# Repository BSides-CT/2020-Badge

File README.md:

# 2020-Badge
Source code, schematics, and advice for hacking the 2020 BSidesCT electronic badge.

## TL;DR

- Software to blink the LEDs on the badge is functional, and you can get it here: [Software/LEDBlink](https://github.com/BSides-CT/2020-Badge/tree/main/Software/LEDBlink)
- Software to use the NFC reader on the badge is not functional, and you can get it here: [Software/NFCBadge](https://github.com/BSides-CT/2020-Badge/tree/main/Software/NFCBadge)
- Read on for more information about what works, what doesn't, and what challenges you are likely to encounter while hacking the badge.

## The Long and Sad Tale of the BSidesCT ~~2019~~ 2020 Badge

### Part 1: Prologue

It started in 2019 when we had a great idea to make a badge with an NFC card reader built into it. We were inspired by the [NFCopy85](https://salmg.net/2019/06/16/nfcopy85/) project and wanted to do something like it. After all, how cool would it be to use your BSidesCT badge to replay hotel key cards, smart locks, or credit card transactions?!

We designed the badge, ordered the PCBs, and started working on the software. We thought we gave sufficient lead time for the boards to be cut and shipped from China...but alas, they arrived to late to be distributed at last year's conference (hence the swell DIY badges we ~~threw together at the last possible second~~ ended up with).

As it turns out, we were doomed to failure last year – even if the badges had arrived on time, we could not have anticipated the other problems we had yet to discover....

### Part 2: Down the Rabbit Hole

The PCBs and other parts finally arrived after BSidesCT 2019 had come and gone, but we found solace in the idea that we could finish them for distribution in 2020. Unfortunately for us, a couple of things made that effort significantly harder:

1. The badge's original designer ghosted us, leaving the 2020 team without design schematics.
2. No working software had yet been produced.

Undeterred, we set out to crack this nut, or at the very least make some LEDs blink. It was pretty obvious from examining the board and components that it had been designed with three main features:

- Cortex-based microcontroller
- NFC chip
- USB-C port

There were also six contact pads arranged in a way that looked like Serial Wire Debug (SWD/JTAG), which should provide a way to program the microcontroller.

From there, we started examining traces, mapping pins, testing connectivity, and generally trying to figure out What Stuff Does™. After many interations and improvements, we finally identified the exact components and pinouts in use. Without further ado, here they are.

#### Microcontroller: Atmel SAM D11 D14AM

- [Datasheet summary](https://github.com/BSides-CT/2020-Badge/blob/main/Hardware/Atmel-SAM-D11-Summary.pdf)
- [Datasheet](https://github.com/BSides-CT/2020-Badge/blob/main/Hardware/Atmel-SAM-D11-Datasheet.pdf)
- Pinout:

#### NFC: CR95HF

- [Datasheet](https://github.com/BSides-CT/2020-Badge/blob/main/Hardware/CR95HF-Datasheet.pdf)
- Pinout:

We did not identify any additional storage components, so the 16 KB of flash storage available on the SAMD11 was all we would have to work with.

In order to program the badge, we acquired a [J-Link EDU Mini](https://www.segger.com/products/debug-probes/j-link/models/j-link-edu-mini/) (later replaced with an [Atmel ICE](https://www.microchip.com/DevelopmentTools/ProductDetails/atatmel-ice)) and relied on our trusty multimeter to map the SWD pinout on the PCB:

We soldered on some wires, plugged them into the J-Link, and fired up [Atmel Studio](https://www.microchip.com/mplab/avr-support/atmel-studio-7) to write some code.

### Part 3: Progress at Last!

Thanks to Atmel Start, it was pretty simple at that point to load up some basic drivers for the SAMD11AM, identify which pins had LEDs attached to them, and write some basic code to make them blink. The J-Link worked like a charm for this simple task.

We added in some functions to make the LEDs blink in fun patterns and decided that, if nothing else, at least we could ship the badges with [that simple program](https://github.com/BSides-CT/2020-Badge/tree/main/Software/LEDBlink). Feel free to customize it to blink however you want it to!

### Part 4: Straight into a Wall

Having enjoyed a fleeting moment of accomplishment, we got back to work on trying to figure out how to get the other components working. The initial goals were pretty simple:

1. Have the CR95HF scan until it found an NFC tag it recognized.
2. Output feedback while scanning to a serial terminal over USB.

Fortunately, Atmel Start also makes it pretty simple to support these features. From the traces on the PCB, we were able to determine that the MCU was intended to communicate with the CR95HF via SPI and not UART, so we knew we would need SPI drivers. We also learned that in order to have the USB port be recognized by another device (i.e. a computer) as a serial terminal (virtual COM port), we would need to configure it as a CDC device.

We configured Atmel Start with the appropriate drivers, mapped the pins appropriately, and then spent a lot of time fussing with the clock configurations (and datasheets) to get everything playing nicely. In the end, this is what our driver stack and clock configs looked like:

The project compiled successfully with the USB drivers, and when we plugged the badge into a computer, it showed up as a COM port in the Device Manager (hooray!). Unfortunately, this is where our luck began to run out. We tried to get the badge to print simple text messages to serial output over USB, but no matter how we attempted to connect to the virtual terminal (or at what baud rate), no messages were ever displayed. We did some troubleshooting and were able to determine that the USB drivers initiated successfully and the serial write function completed successfully, so we were mystified about where communication broke down.

### Part 5: Left Hanging

Not longer after this development, we finally managed to get in touch with the original designer, who sent us the [KiCad design schematics](https://github.com/BSides-CT/2020-Badge/tree/main/Hardware/Schematics) and non-functioning prototype software. This information confirmed many of the determinations we had made, corrected several of our mistakes, and gave us a jump on the software to use to run the CR95HF. Unfortunately, despite being able to integrate much of that code into our own project, we quickly ran into a deal-breaker as the CR95HF failed to initialize. Without serial output, of course, we found this exceedingly hard to debug, and mostly relied on the LEDs to test whether specific functions succeeded or failed.

In the end, we ran out of time and decided it would be best to deliver the badges with some nice blinking lights and a link to a GitHub repo with all the information one needs to pick up where we left off. There is a still a great deal of potential in this project for those who are more knowledgable than our scrappy band of misfits!

Our hope is that someone will solve one or two of the problems that held us up and find a way to make the badge do something more interesting than just blink its LEDs! If that person is you, please reach out to us at info@bsidesct.org and we'll be excited to trade notes.

### Epilogue: Known Issues

Along the way, we discovered several problems that stopped us from reaching our initial goal. Here they are, for the reader's edification:

- We were unable to get USB working as a functional virtual com port. The designer suspected there might have been a design or manufacturing flaw involved, but this year's team did not have enough electrical engineering knowledge to verify this. You can power the badge via USB.

- We were unable to get the CR95HF to initalize successfully. The initialization sequence involves a loop that continually tests for a response from the chip before moving on, but it never escapes that loop.

- While testing basic components, we started to run out of storage space. If you manage to get the NFC chip functional, it is likely you will need to get creative about managing data to make the badge do anything interesting.

- Programming the badges en masse proved to be a challenge, as the SWD pin pads do not map to any standard configuration. As such, we had to build our own adapter to remap the standard 10-pin cable from our Atmel ICE programmer to a standard 6-pin TC2030 programming cable.

  We don't recommend doing it this way, which was only really necessary for mass production – you're better off just soldering wires onto the badge to program it. Follow the SWD pinout we posted above, and you should be good to go!

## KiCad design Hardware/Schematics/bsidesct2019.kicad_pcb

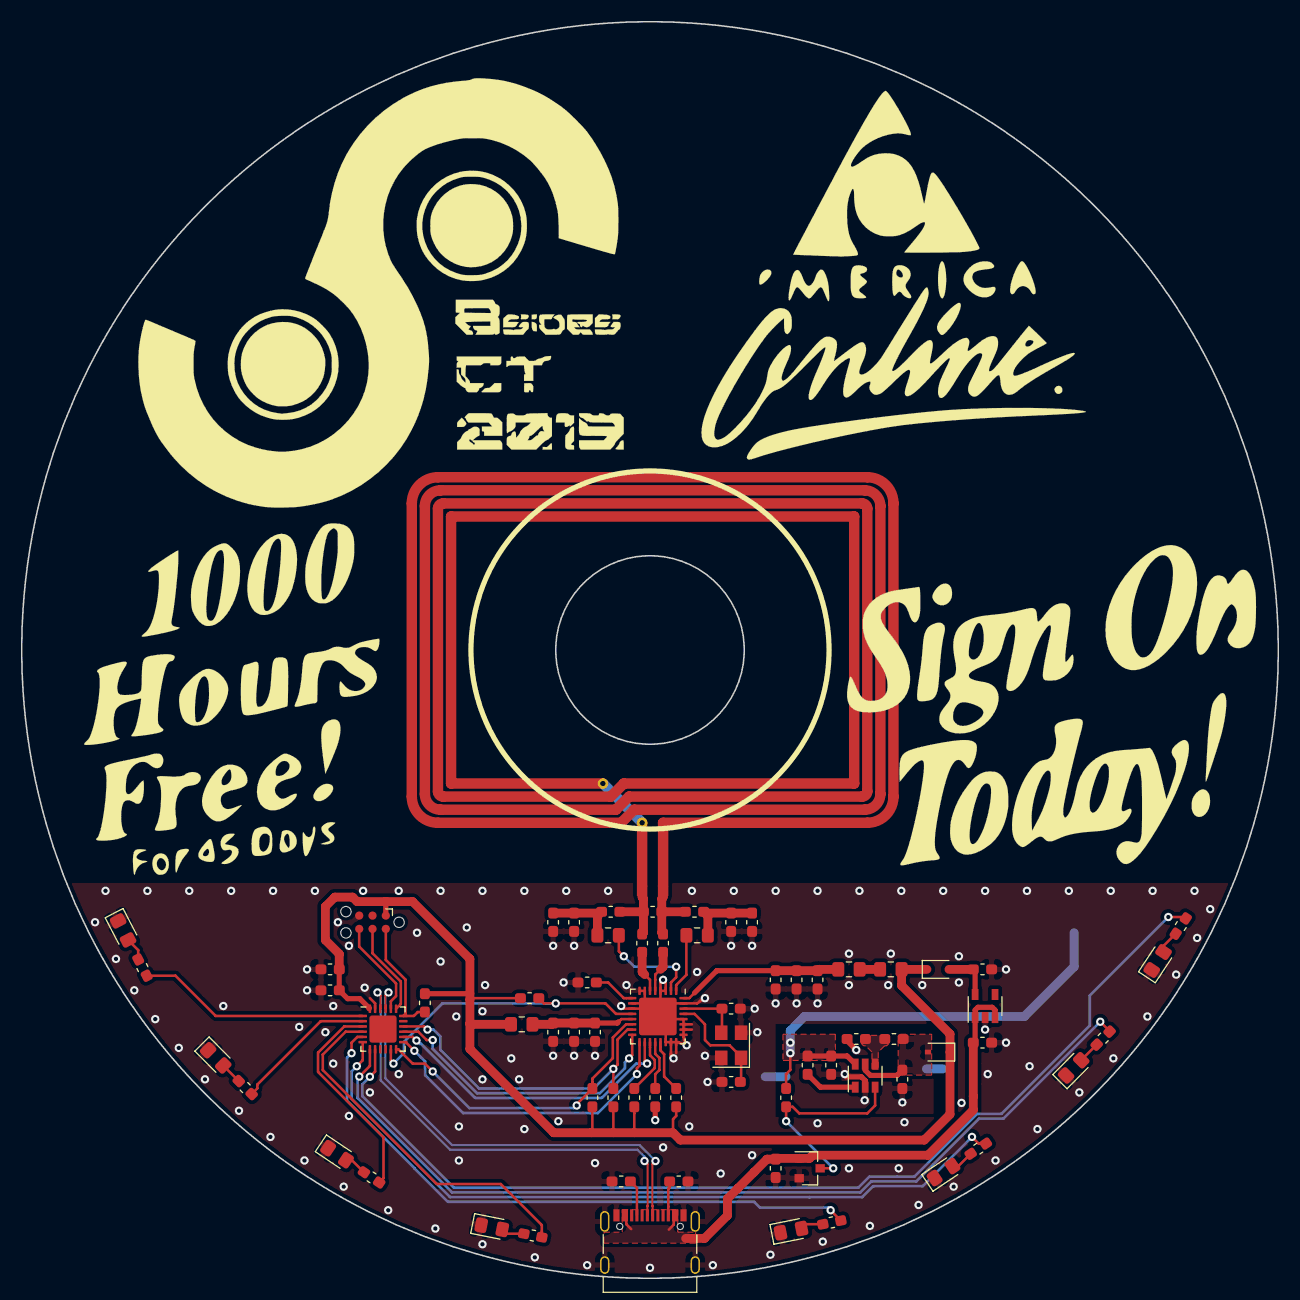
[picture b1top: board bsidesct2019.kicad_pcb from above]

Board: 2 copper layers, 120.0 x 120.0 mm, 75 parts (1 on the bottom side), 55 nets.

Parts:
AE1: Antenna; CR95HF-antenna
C1, C2, C18, C21, C22: 1uF; C_0603_1608Metric_Pad1.05x0.95mm_HandSolder
C3, C4, C10: 0.1uF; C_0603_1608Metric_Pad1.05x0.95mm_HandSolder
C5, C9: 10pF; C_0603_1608Metric_Pad1.05x0.95mm_HandSolder
C6, C7: 10nF; C_0603_1608Metric_Pad1.05x0.95mm_HandSolder
C8: 1nF; C_0603_1608Metric_Pad1.05x0.95mm_HandSolder
C11, C12, C13, C14: 100pF; C_0603_1608Metric_Pad1.05x0.95mm_HandSolder
C15, C16: 47pF; C_0603_1608Metric_Pad1.05x0.95mm_HandSolder
C17: 82pF; C_0603_1608Metric_Pad1.05x0.95mm_HandSolder
C19: 4.7uF; C_0603_1608Metric_Pad1.05x0.95mm_HandSolder
C20: 10uF; C_0603_1608Metric_Pad1.05x0.95mm_HandSolder
D1, D10: CUS10S30,H3F; D_SOD-323
D2, D3, D4, D5, D6, D7, D8, D9: LED; LED_0805_2012Metric_Pad1.15x1.40mm_HandSolder
J1: TC2030; Tag-Connect_TC2030-IDC-NL_2x03_P1.27mm_Vertical
L1, L2, L3: 742792042; L_0805_2012Metric_Pad1.15x1.40mm_HandSolder
L4, L5: 560nH; L_0805_2012Metric_Pad1.15x1.40mm_HandSolder
L6: 4.7uH; L_0603_1608Metric_Pad1.05x0.95mm_HandSolder
P1: USB_C_Plug_USB2.0; USB_C_Receptacle_Palconn_UTC16-G
Q1: 2N7002; SOT-23
R1, R2, R3, R4, R5, R15: 3.3kΩ; R_0603_1608Metric_Pad1.05x0.95mm_HandSolder
R6, R7: 330Ω; R_0603_1608Metric_Pad1.05x0.95mm_HandSolder
R8, R13, R14: 10kΩ; R_0603_1608Metric_Pad1.05x0.95mm_HandSolder
R9, R10: 5.1kΩ; R_0603_1608Metric_Pad1.05x0.95mm_HandSolder
R11: 976kΩ; R_0603_1608Metric_Pad1.05x0.95mm_HandSolder
R12: 562kΩ; R_0603_1608Metric_Pad1.05x0.95mm_HandSolder
R16, R17, R18, R19, R20, R21, R22, R23: 260Ω; R_0603_1608Metric_Pad1.05x0.95mm_HandSolder
Ref**: Val**; twitter
Ref**#2: Val**; aol_3
Ref**#3: Val**; aol_2
Ref**#4: Val**; aol_1-merica
Ref**#5: Val**; bsidesct.2019.logo.transparent
U1: CR95HF; QFN-32-1EP_5x5mm_P0.5mm_EP3.6x3.6mm
U2: MCP1640BCH; SOT-23-6
U3: ATSAMD11D14A-M; QFN-24-1EP_4x4mm_P0.5mm_EP2.6x2.6mm
U4: MIC5504-3.3YM5-TR; SOT-23-5
Y1: 27.12MHz; Crystal_SMD_SeikoEpson_FA238V-4Pin_3.2x2.5mm

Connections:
+3V3: C10.1, C18.1, D1.1, D10.1, J1.1, L1.1, L3.1, R1.1, R2.1, R3.1, R5.1, R8.1, R15.1, U3.24
+5V: C21.1, P1.A4, P1.A9, P1.B4, P1.B9, Q1.1, R13.1, U4.1, U4.3
+BATT: C19.1, L6.1, R14.1, U2.6
/D+: P1.A6, U3.22
/D-: P1.A7, U3.21
/L0: R16.2, U3.1
/L1: R17.2, U3.2
/L2: R18.2, U3.3
/L3: R19.2, U3.4
/L4: R20.1, U3.5
/L5: R21.1, U3.6
/L6: R22.1, U3.7
/L7: R23.1, U3.8
/MISO: U1.16, U3.15
/MOSI: U1.17, U3.13
/RX: R3.2, U1.14, U3.12
/SCK: U1.18, U3.14
/SS: R15.2, U1.15, U3.16
/TX: R2.2, U1.12, U3.11
GND: C1.2, C2.2, C3.2, C4.2, C5.2, C6.2, C7.2, C8.1, C9.2, C10.2, C11.2, C12.1, C13.2, C14.1, C18.2, C19.2, C20.2, C21.2, C22.2, D2.1, D3.1, D4.1, D5.1, D6.1, D7.1, D8.1, D9.1, J1.5, P1.A1, P1.A12, P1.B1, P1.B12, P1.S1, Q1.2, R4.1, R9.2, R10.2, R12.2, R13.2, U1.3, U1.4, U1.7, U1.8, U1.10, U1.11, U1.22, U1.23, U1.24, U1.25, U1.26, U1.27, U1.28, U1.31, U1.33, U2.2, U3.23, U4.2, Y1.2, Y1.4
unnamed: AE1.1, C15.2, C17.1, R6.1
unnamed: AE1.2, C16.2, C17.2, R7.1
unnamed: C1.1, C3.1, C6.1, L2.2, U1.32
unnamed: C2.1, C4.1, C7.1, L3.2, U1.13
unnamed: C5.1, U1.29, Y1.1
unnamed: C8.2, U1.9
unnamed: C9.1, U1.30, Y1.3
unnamed: C11.1, C13.1, C15.1, L4.2
unnamed: C12.2, C14.2, C16.1, L5.2
unnamed: C20.1, D1.2, R11.1, U2.5
unnamed: C22.1, D10.2, U4.5
unnamed: D2.2, R16.1
unnamed: D3.2, R17.1
unnamed: D4.2, R18.1
unnamed: D5.2, R19.1
unnamed: D6.2, R20.2
unnamed: D7.2, R21.2
unnamed: D8.2, R22.2
unnamed: D9.2, R23.2
unnamed: J1.2, R8.2, U3.18
unnamed: J1.4, U3.19
unnamed: J1.6, U3.20
unnamed: L1.2, L2.1
unnamed: L4.1, U1.1
unnamed: L5.1, U1.2
unnamed: L6.2, U2.1
unnamed: P1.A5, R9.1
unnamed: P1.B5, R10.1
unnamed: Q1.3, R14.2, U2.3
unnamed: R1.2, U1.19
unnamed: R4.2, U1.20
unnamed: R5.2, U1.21
unnamed: R6.2, U1.5
unnamed: R7.2, U1.6
unnamed: R11.2, R12.1, U2.4

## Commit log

2020-11-04 Initial hw/sw commit
2020-11-11 Write badge story
2020-11-11 Fix images
